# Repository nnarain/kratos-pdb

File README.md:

# Kratos PDB

A simple power distribution board for personal projects.

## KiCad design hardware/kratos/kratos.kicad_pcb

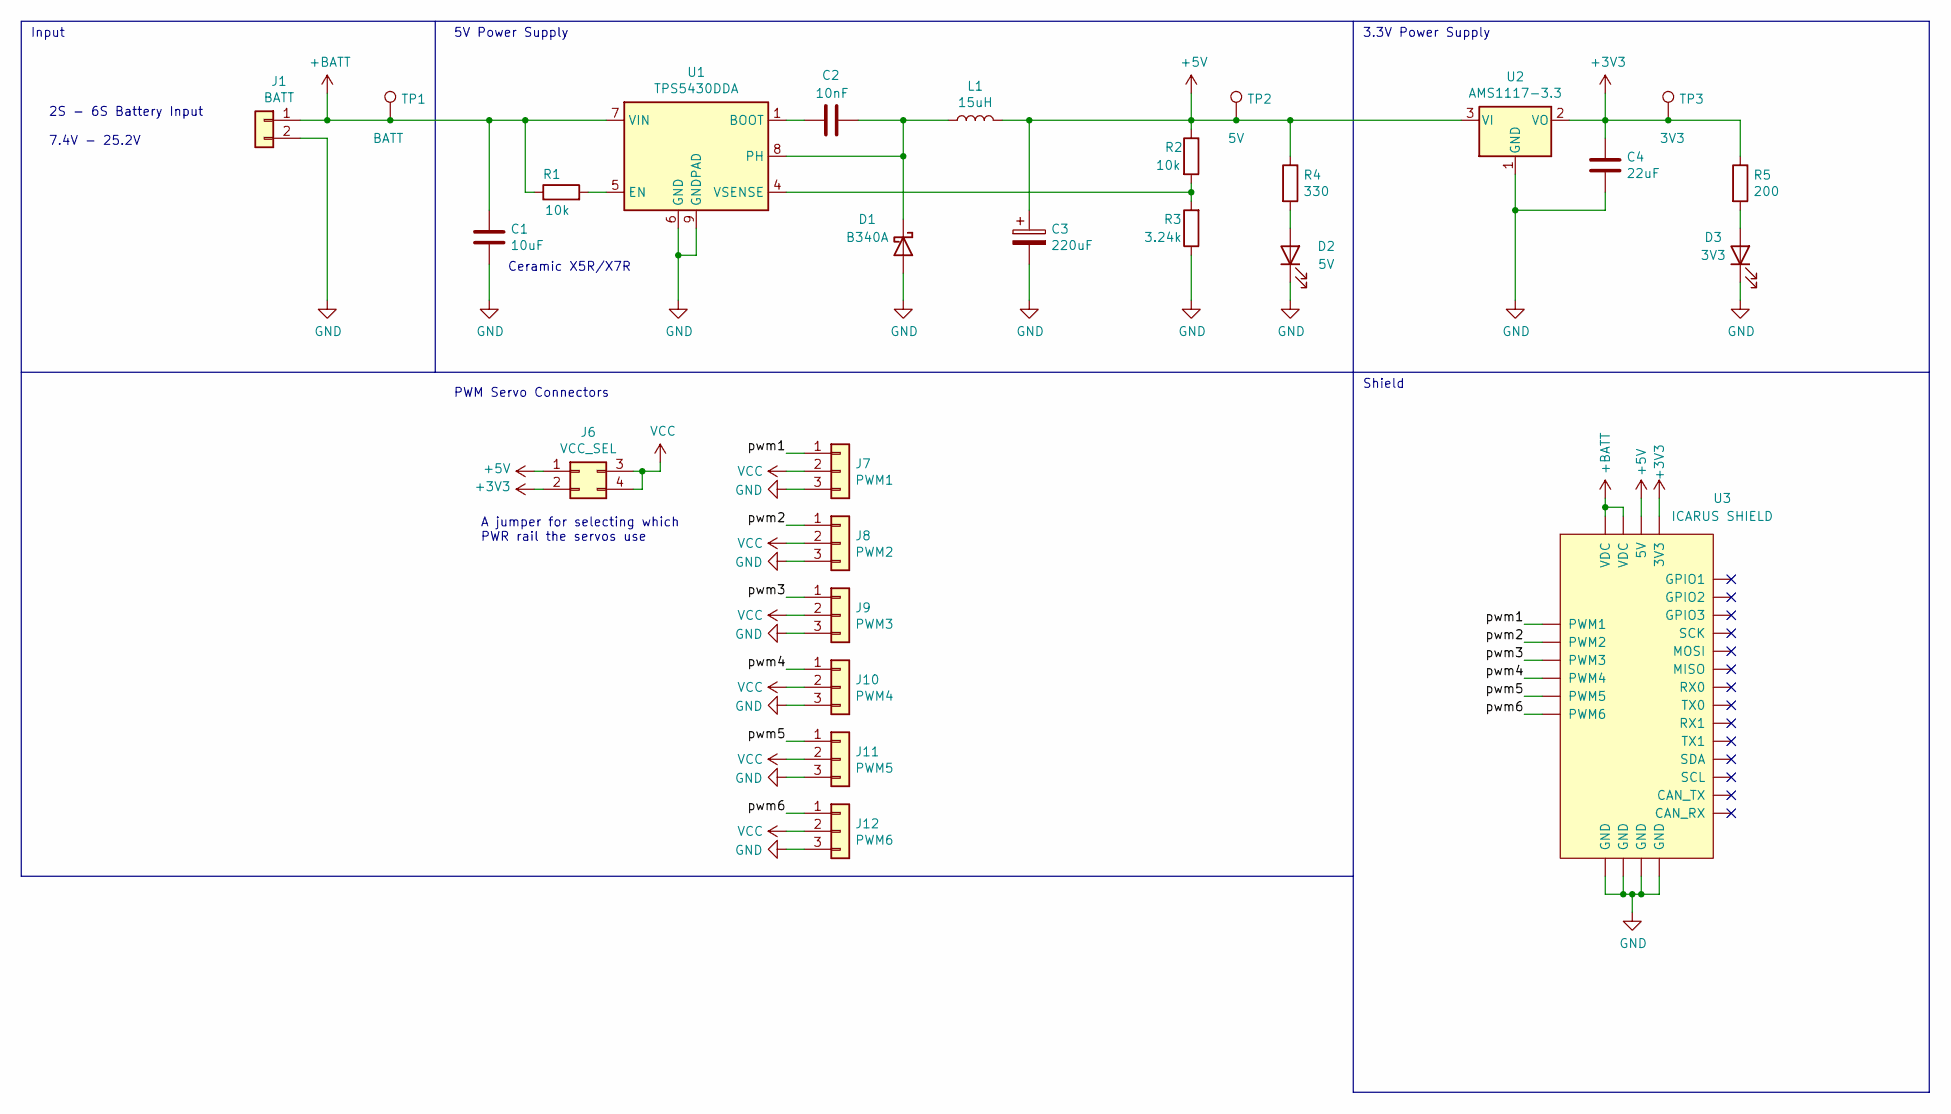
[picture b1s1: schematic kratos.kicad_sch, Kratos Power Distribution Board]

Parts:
C1: 10uF; C_0805_2012Metric; LCSC C440198
C2: 10nF; C_0805_2012Metric; LCSC C1710
C3: 220uF; CP_Elec_6.3x5.4; LCSC C3345
C4: 22uF; CP_EIA-3216-18_Kemet-A; LCSC C116575
D1: B340A; D_SMA; LCSC C64982
D2: 5V; LED_0805_2012Metric; LCSC C95814
D3: 3V3; LED_0805_2012Metric; LCSC C95814
J1: BATT; XT60
J6: VCC_SEL; PinSocket_2x02_P2.54mm_Vertical
J7: PWM1; PinSocket_1x03_P2.54mm_Vertical
J8: PWM2; PinSocket_1x03_P2.54mm_Vertical
J9: PWM3; PinSocket_1x03_P2.54mm_Vertical
J10: PWM4; PinSocket_1x03_P2.54mm_Vertical
J11: PWM5; PinSocket_1x03_P2.54mm_Vertical
J12: PWM6; PinSocket_1x03_P2.54mm_Vertical
L1: 15uH; MWSA0603S-150MT; LCSC C408452
R1, R2: 10k; R_0805_2012Metric; LCSC C17408
R3: 3.24k; R_0805_2012Metric; LCSC C64285
R4: 330; R_0805_2012Metric; LCSC C17630
R5: 200; R_0805_2012Metric; LCSC C17540
TP1: BATT; TestPoint_Pad_2.0x2.0mm
TP2: 5V; TestPoint_Pad_2.0x2.0mm
TP3: 3V3; TestPoint_Pad_2.0x2.0mm
U1: TPS5430DDA; TI_SO-PowerPAD-8_ThermalVias; LCSC C9864
U2: AMS1117-3.3; SOT-223-3_TabPin2; LCSC C6186
U3: ICARUS SHIELD; icarus-shield

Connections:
+3V3: C4.1, J6.2, R5.1, TP3.1, U2.2 (VO), U3.8 (3V3)
+5V: C3.1, J6.1, L1.2, R2.1, R4.1, TP2.1, U2.3 (VI), U3.6 (5V)
+BATT: C1.1, J1.1, R1.1, TP1.1, U1.7 (VIN), U3.2 (VDC), U3.4 (VDC)
/pwm1: J7.1, U3.9 (PWM1)
/pwm2: J8.1, U3.10 (PWM2)
/pwm3: J9.1, U3.11 (PWM3)
/pwm4: J10.1, U3.12 (PWM4)
/pwm5: J11.1, U3.13 (PWM5)
/pwm6: J12.1, U3.14 (PWM6)
GND: C1.2, C3.2, C4.2, D1.2 (A), D2.1 (K), D3.1 (K), J1.2, J7.3, J8.3, J9.3, J10.3, J11.3, J12.3, R3.1, U1.6 (GND), U1.9 (GNDPAD), U2.1 (GND), U3.1 (GND), U3.3 (GND), U3.5 (GND), U3.7 (GND)
unnamed: C2.1, U1.1 (BOOT)
unnamed: C2.2, D1.1 (K), L1.1, U1.8 (PH)
unnamed: D2.2 (A), R4.2
unnamed: D3.2 (A), R5.2
unnamed: R1.2, U1.5 (EN)
unnamed: R2.2, R3.2, U1.4 (VSENSE)
VCC: J6.3, J6.4, J7.2, J8.2, J9.2, J10.2, J11.2, J12.2

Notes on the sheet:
3.3V Power Supply
Shield
2S - 6S Battery Input 7.4V - 25.2V
A jumper for selecting which PWR rail the servos use
5V Power Supply
Ceramic X5R/X7R
Input
PWM Servo Connectors

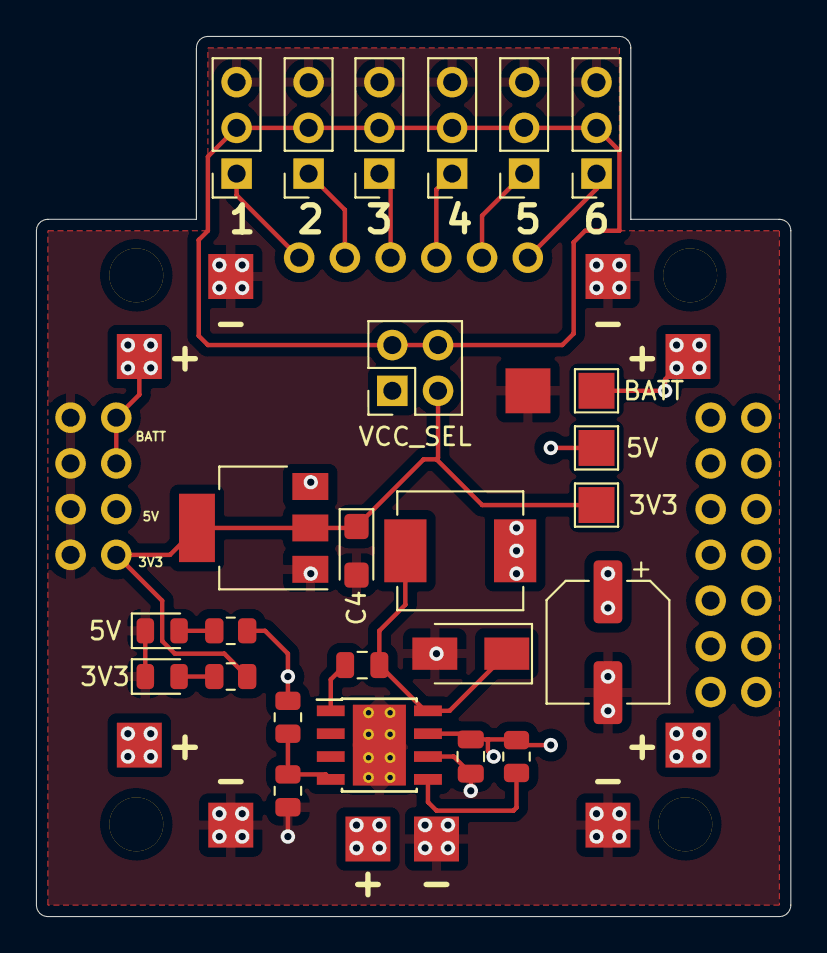
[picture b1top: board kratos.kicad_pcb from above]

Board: 4 copper layers, 41.9 x 48.9 mm, 27 parts (0 on the bottom side), 17 nets.

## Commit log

2021-03-08 Initial design schematic
2021-03-17 Update to linear regulators. Added PCB layout
2021-03-17 Update git ignore
2021-03-18 update text
2021-03-19 Update digikey part numbers in schematics
2021-03-19 Update tantalum cap to polarized
2021-04-17 Update part number
2021-04-17 Resolved #1. Docs and Github Actions
2021-04-17 deploy: 5e5c2f752f8092ffffa85ac0e784dbeaddbbb724
2021-09-06 Rev B
2021-09-06 deploy: 37991213f0a30d19cb01335768115adfc7f8192c
2021-12-06 Layer update
2022-01-08 REV C
2022-01-26 Fix 10k resistor JLCPCB selection
2022-02-24 Kibot config. Updated book
2022-02-24 deploy: d3f23d83129573f9082af12d2af72a914036e8ad
2022-02-24 clean up release workflow
2022-02-24 deploy: 422c28aa2635200ecdeab63de9e93a519d0c0344
